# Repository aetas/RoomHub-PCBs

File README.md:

# RoomHub 3 PCBs

> :warning: RoomHub project is now deprecated in favor of [MqGateway](https://github.com/aetas/mqgateway) project.

<br />

Schematics and PCB design for RoomHub 3 MainBoard and IOBoard

Files can be read with [KiCad](https://kicad-pcb.org).

Read more about RoomHub on [documentation page](https://aetas.github.io/RoomHub/).

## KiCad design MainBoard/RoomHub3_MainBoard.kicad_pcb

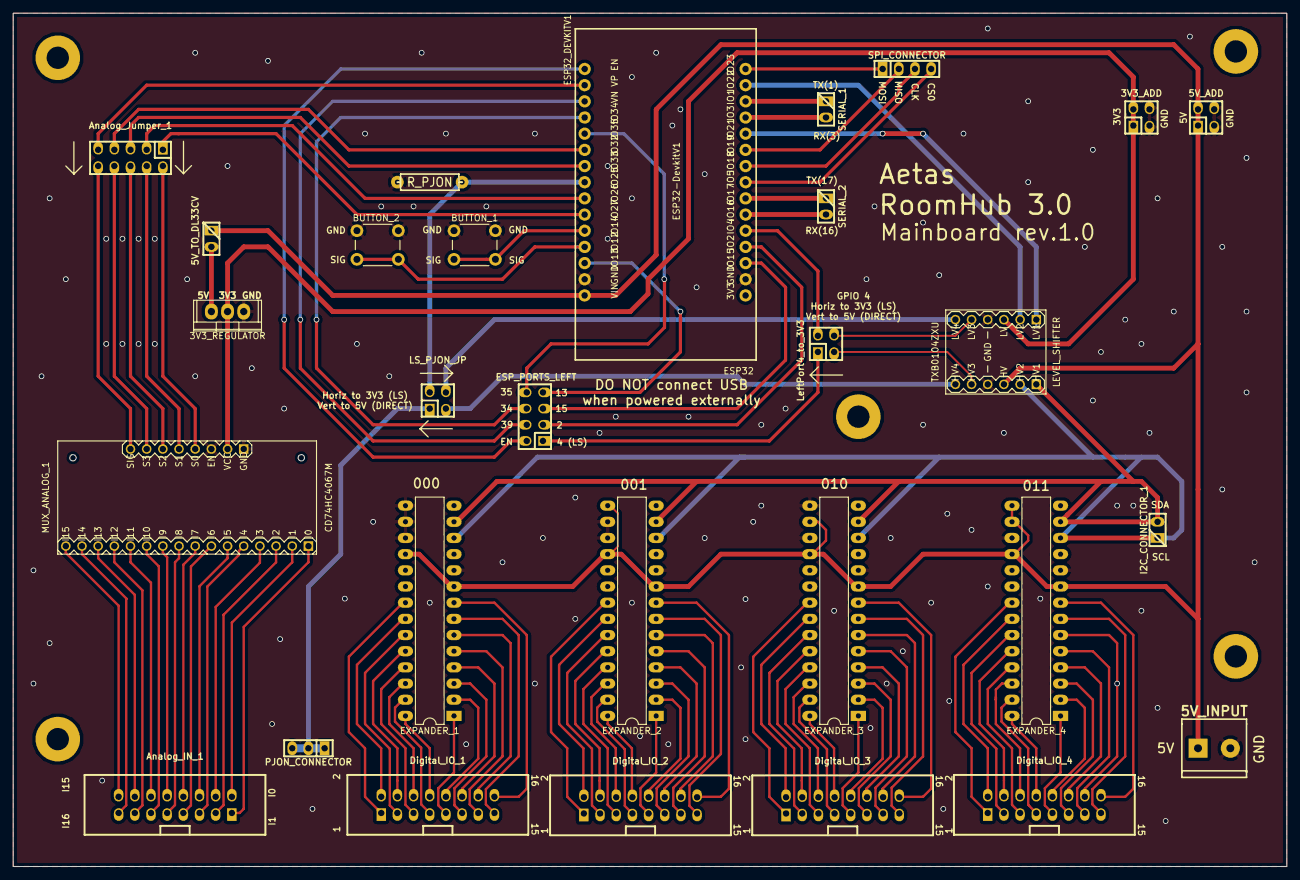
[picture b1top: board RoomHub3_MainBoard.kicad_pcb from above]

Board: 2 copper layers, 200.0 x 134.0 mm, 29 parts (0 on the bottom side), 123 nets.

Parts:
3V3_ADD, 5V_ADD: Conn_02x02_RAW; pin_strip_2x2
3V3_REGULATOR: LD33CV; TO-220
5V_INPUT: mors_2p
5V_TO_DL33CV: Jumper; pin_strip_2
Analog_IN_1: Conn_02x08_Counter_Clockwise; analog_conn_02x08
Analog_Jumper_1: Jumper_2x5; pin_strip_5x2
BUTTON_1, BUTTON_2: SW_Push; SW_PUSH_6mm
Digital_IO_1, Digital_IO_2, Digital_IO_3, Digital_IO_4: Conn_02x08_Counter_Clockwise; vasch_strip_8x2
ESP32: ESP32_DEVKITV1; ESP32-DEVKITV1
ESP_PORTS_LEFT: Conn_02x04_Counter_Clockwise; pin_strip_4x2
EXPANDER_1, EXPANDER_2, EXPANDER_3, EXPANDER_4: MCP23017_SP; DIP-28_W7.62mm_LongPads
I2C_CONNECTOR_1: Conn_01x02; pin_strip_2
LEVEL_SHIFTER: TXB0104ZXU; LEVEL-SHIFTER-4CH
LS_PJON_JP: Conn_02x02_RAW; pin_strip_2x2
LeftPort4_to_3V3: Conn_02x02_RAW; pin_strip_2x2
MUX_ANALOG_1: CD74HC4067M; SPARKFUN-AD-MUX-16X1-aetas
PJON_CONNECTOR: Conn_01x03; pin_strip_3
R_PJON: 2.2K; RC05
SERIAL_1, SERIAL_2: Conn_01x02; pin_strip_2
SPI_CONNECTOR: Conn_01x04; pin_strip_4

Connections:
+5V: 5V_ADD.1, 5V_ADD.2, 5V_INPUT.1, 5V_TO_DL33CV.1, ESP32.30, EXPANDER_1.9, EXPANDER_1.18, EXPANDER_2.9, EXPANDER_2.15, EXPANDER_2.18, EXPANDER_3.9, EXPANDER_3.16, EXPANDER_3.18, EXPANDER_4.9, EXPANDER_4.15, EXPANDER_4.16, EXPANDER_4.18, LEVEL_SHIFTER.B1
/3V3: 3V3_ADD.1, 3V3_ADD.2, 3V3_REGULATOR.2, LEVEL_SHIFTER.B2, MUX_ANALOG_1.24
/SCL1: ESP32.14, LEVEL_SHIFTER.A2
/SDA1: ESP32.11, LEVEL_SHIFTER.A1
GND: 3V3_ADD.3, 3V3_ADD.4, 3V3_REGULATOR.1, 5V_ADD.3, 5V_ADD.4, 5V_INPUT.2, BUTTON_1.1, BUTTON_2.1, ESP32.2, ESP32.29, EXPANDER_1.10, EXPANDER_1.15, EXPANDER_1.16, EXPANDER_1.17, EXPANDER_2.10, EXPANDER_2.16, EXPANDER_2.17, EXPANDER_3.10, EXPANDER_3.15, EXPANDER_3.17, EXPANDER_4.10, EXPANDER_4.17, LEVEL_SHIFTER.B3, LEVEL_SHIFTER.B4, MUX_ANALOG_1.12, MUX_ANALOG_1.15, R_PJON.1
unnamed: 3V3_REGULATOR.3, 5V_TO_DL33CV.2
unnamed: Analog_IN_1.1, MUX_ANALOG_1.9
unnamed: Analog_IN_1.2, MUX_ANALOG_1.8
unnamed: Analog_IN_1.3, MUX_ANALOG_1.7
unnamed: Analog_IN_1.4, MUX_ANALOG_1.6
unnamed: Analog_IN_1.5, MUX_ANALOG_1.5
unnamed: Analog_IN_1.6, MUX_ANALOG_1.4
unnamed: Analog_IN_1.7, MUX_ANALOG_1.3
unnamed: Analog_IN_1.8, MUX_ANALOG_1.2
unnamed: Analog_IN_1.9, MUX_ANALOG_1.23
unnamed: Analog_IN_1.10, MUX_ANALOG_1.22
unnamed: Analog_IN_1.11, MUX_ANALOG_1.21
unnamed: Analog_IN_1.12, MUX_ANALOG_1.20
unnamed: Analog_IN_1.13, MUX_ANALOG_1.19
unnamed: Analog_IN_1.14, MUX_ANALOG_1.18
unnamed: Analog_IN_1.15, MUX_ANALOG_1.17
unnamed: Analog_IN_1.16, MUX_ANALOG_1.16
unnamed: Analog_Jumper_1.1, ESP32.25
unnamed: Analog_Jumper_1.2, MUX_ANALOG_1.10
unnamed: Analog_Jumper_1.3, ESP32.24
unnamed: Analog_Jumper_1.4, MUX_ANALOG_1.11
unnamed: Analog_Jumper_1.5, ESP32.22
unnamed: Analog_Jumper_1.6, MUX_ANALOG_1.14
unnamed: Analog_Jumper_1.7, ESP32.21
unnamed: Analog_Jumper_1.8, MUX_ANALOG_1.13
unnamed: Analog_Jumper_1.9, ESP32.17
unnamed: Analog_Jumper_1.10, MUX_ANALOG_1.1
unnamed: Digital_IO_1.1, EXPANDER_1.21
unnamed: Digital_IO_1.2, EXPANDER_1.22
unnamed: Digital_IO_1.3, EXPANDER_1.23
unnamed: Digital_IO_1.4, EXPANDER_1.24
unnamed: Digital_IO_1.5, EXPANDER_1.25
unnamed: Digital_IO_1.6, EXPANDER_1.26
unnamed: Digital_IO_1.7, EXPANDER_1.27
unnamed: Digital_IO_1.8, EXPANDER_1.28
unnamed: Digital_IO_1.9, EXPANDER_1.1
unnamed: Digital_IO_1.10, EXPANDER_1.2
unnamed: Digital_IO_1.11, EXPANDER_1.3
unnamed: Digital_IO_1.12, EXPANDER_1.4
unnamed: Digital_IO_1.13, EXPANDER_1.5
unnamed: Digital_IO_1.14, EXPANDER_1.6
unnamed: Digital_IO_1.15, EXPANDER_1.7
unnamed: Digital_IO_1.16, EXPANDER_1.8
unnamed: Digital_IO_2.1, EXPANDER_2.21
unnamed: Digital_IO_2.2, EXPANDER_2.22
unnamed: Digital_IO_2.3, EXPANDER_2.23
unnamed: Digital_IO_2.4, EXPANDER_2.24
unnamed: Digital_IO_2.5, EXPANDER_2.25
unnamed: Digital_IO_2.6, EXPANDER_2.26
unnamed: Digital_IO_2.7, EXPANDER_2.27
unnamed: Digital_IO_2.8, EXPANDER_2.28
unnamed: Digital_IO_2.9, EXPANDER_2.1
unnamed: Digital_IO_2.10, EXPANDER_2.2
unnamed: Digital_IO_2.11, EXPANDER_2.3
unnamed: Digital_IO_2.12, EXPANDER_2.4
unnamed: Digital_IO_2.13, EXPANDER_2.5
unnamed: Digital_IO_2.14, EXPANDER_2.6
unnamed: Digital_IO_2.15, EXPANDER_2.7
unnamed: Digital_IO_2.16, EXPANDER_2.8
unnamed: Digital_IO_3.1, EXPANDER_3.21
unnamed: Digital_IO_3.2, EXPANDER_3.22
unnamed: Digital_IO_3.3, EXPANDER_3.23
unnamed: Digital_IO_3.4, EXPANDER_3.24
unnamed: Digital_IO_3.5, EXPANDER_3.25
unnamed: Digital_IO_3.6, EXPANDER_3.26
unnamed: Digital_IO_3.7, EXPANDER_3.27
unnamed: Digital_IO_3.8, EXPANDER_3.28
unnamed: Digital_IO_3.9, EXPANDER_3.1
unnamed: Digital_IO_3.10, EXPANDER_3.2
unnamed: Digital_IO_3.11, EXPANDER_3.3
unnamed: Digital_IO_3.12, EXPANDER_3.4
unnamed: Digital_IO_3.13, EXPANDER_3.5
unnamed: Digital_IO_3.14, EXPANDER_3.6
unnamed: Digital_IO_3.15, EXPANDER_3.7
unnamed: Digital_IO_3.16, EXPANDER_3.8
unnamed: Digital_IO_4.1, EXPANDER_4.21
unnamed: Digital_IO_4.2, EXPANDER_4.22
unnamed: Digital_IO_4.3, EXPANDER_4.23
unnamed: Digital_IO_4.4, EXPANDER_4.24
unnamed: Digital_IO_4.5, EXPANDER_4.25
unnamed: Digital_IO_4.6, EXPANDER_4.26
unnamed: Digital_IO_4.7, EXPANDER_4.27
unnamed: Digital_IO_4.8, EXPANDER_4.28
unnamed: Digital_IO_4.9, EXPANDER_4.1
unnamed: Digital_IO_4.10, EXPANDER_4.2
unnamed: Digital_IO_4.11, EXPANDER_4.3
unnamed: Digital_IO_4.12, EXPANDER_4.4
unnamed: Digital_IO_4.13, EXPANDER_4.5
unnamed: Digital_IO_4.14, EXPANDER_4.6
unnamed: Digital_IO_4.15, EXPANDER_4.7
unnamed: Digital_IO_4.16, EXPANDER_4.8
unnamed: ESP32.3, ESP_PORTS_LEFT.5
unnamed: ESP32.4, ESP_PORTS_LEFT.3
unnamed: ESP32.5, LeftPort4_to_3V3.2
unnamed: ESP32.6, SERIAL_2.2
unnamed: ESP32.7, SERIAL_2.1
unnamed: ESP32.8, SPI_CONNECTOR.4
unnamed: ESP32.9, SPI_CONNECTOR.3
unnamed: ESP32.10, SPI_CONNECTOR.2
unnamed: ESP32.12, SERIAL_1.2
unnamed: ESP32.13, SERIAL_1.1
unnamed: ESP32.15, SPI_CONNECTOR.1
unnamed: ESP32.16, ESP_PORTS_LEFT.2
unnamed: ESP32.18, ESP_PORTS_LEFT.4
unnamed: ESP32.19, ESP_PORTS_LEFT.6
unnamed: ESP32.20, ESP_PORTS_LEFT.8
unnamed: ESP32.23, LS_PJON_JP.2, R_PJON.2
unnamed: BUTTON_1.2, ESP32.26
unnamed: BUTTON_2.2, ESP32.27
unnamed: ESP32.28, ESP_PORTS_LEFT.7
unnamed: ESP_PORTS_LEFT.1, LeftPort4_to_3V3.1
unnamed: EXPANDER_1.12, EXPANDER_2.12, EXPANDER_3.12, EXPANDER_4.12, I2C_CONNECTOR_1.1, LEVEL_SHIFTER.C2
unnamed: EXPANDER_1.13, EXPANDER_2.13, EXPANDER_3.13, EXPANDER_4.13, I2C_CONNECTOR_1.2, LEVEL_SHIFTER.C1
unnamed: LEVEL_SHIFTER.A3, LeftPort4_to_3V3.4
unnamed: LEVEL_SHIFTER.A4, LS_PJON_JP.4
unnamed: LEVEL_SHIFTER.C3, LeftPort4_to_3V3.3
unnamed: LEVEL_SHIFTER.C4, LS_PJON_JP.3
unnamed: LS_PJON_JP.1, PJON_CONNECTOR.1, PJON_CONNECTOR.2, PJON_CONNECTOR.3

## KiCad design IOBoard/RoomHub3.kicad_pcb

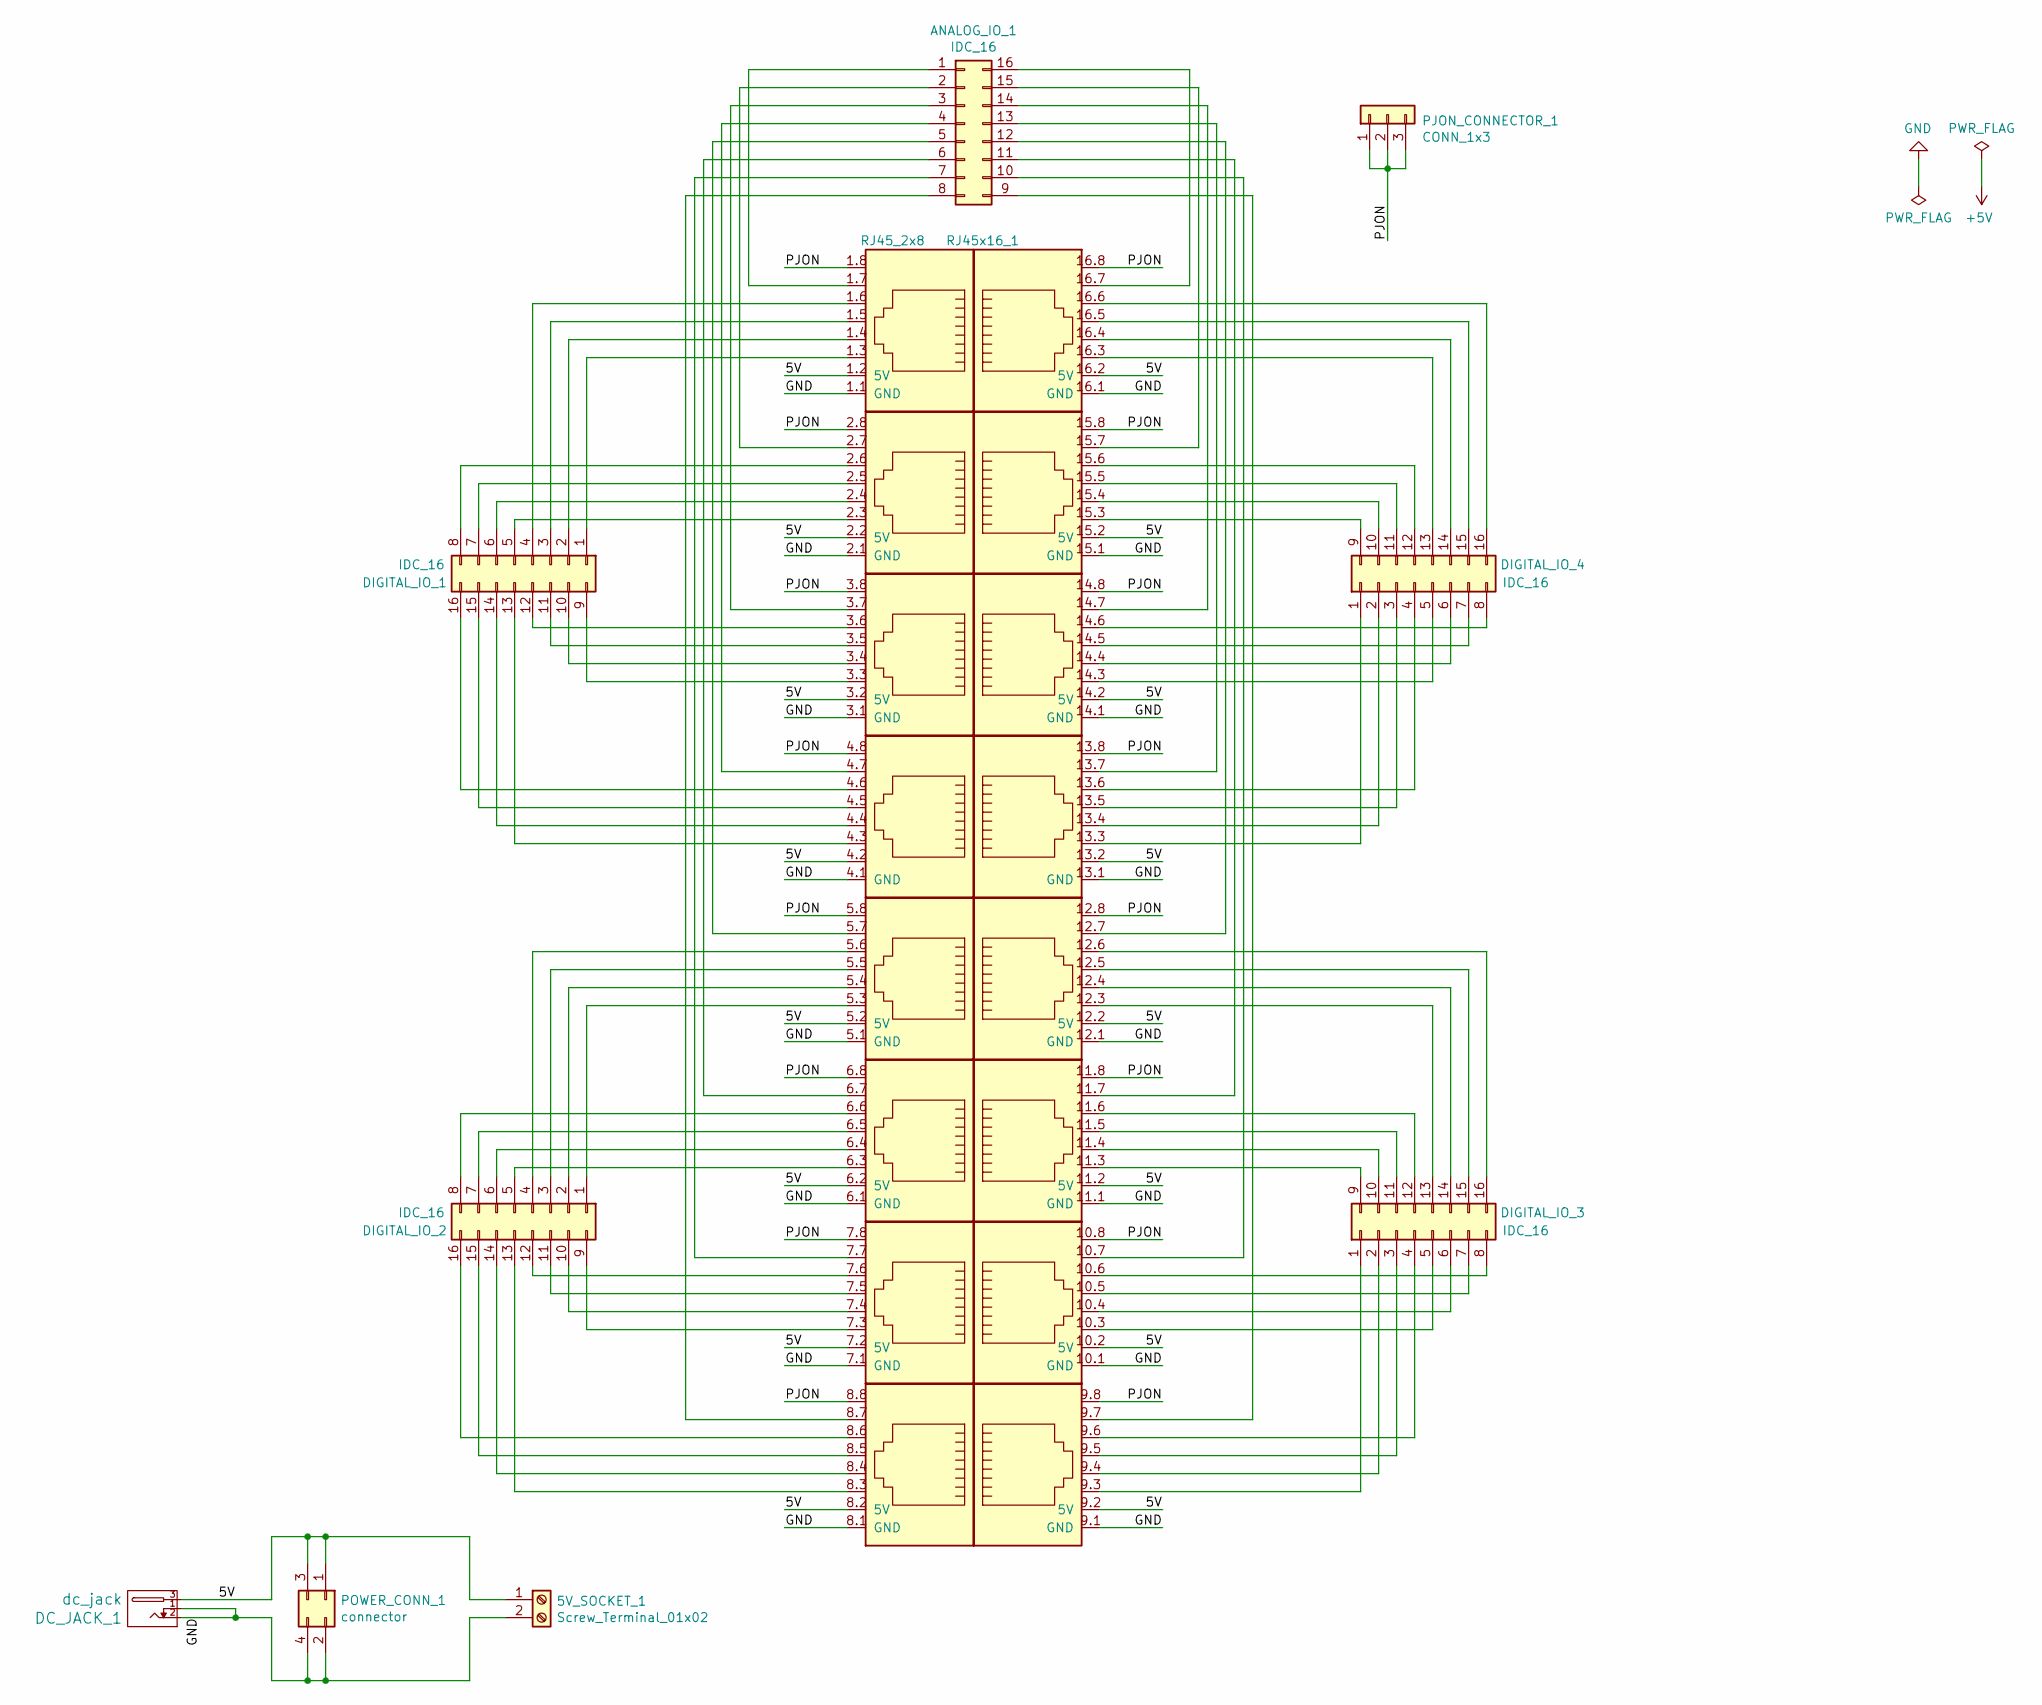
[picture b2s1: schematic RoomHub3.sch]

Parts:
5V_SOCKET_1: Screw_Terminal_01x02; mors_2p
ANALOG_IO_1: IDC_16; analog_conn_02x08
DC_JACK_1: dc_jack; dc_socket
DIGITAL_IO_1, DIGITAL_IO_2, DIGITAL_IO_3, DIGITAL_IO_4: IDC_16; vasch_strip_8x2
PJON_CONNECTOR_1: CONN_1x3; pin_strip_3
POWER_CONN_1: connector; pin_strip_2x2
RJ45x16_1: RJ45_2x8; 8p8c_2x8_roomhub

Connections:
/5V: 5V_SOCKET_1.1, DC_JACK_1.3, POWER_CONN_1.1, POWER_CONN_1.3, RJ45x16_1.1.2 (5V), RJ45x16_1.2.2 (5V), RJ45x16_1.3.2 (5V), RJ45x16_1.4.2, RJ45x16_1.5.2 (5V), RJ45x16_1.6.2 (5V), RJ45x16_1.7.2 (5V), RJ45x16_1.8.2 (5V), RJ45x16_1.9.2 (5V), RJ45x16_1.10.2 (5V), RJ45x16_1.11.2 (5V), RJ45x16_1.12.2 (5V), RJ45x16_1.13.2, RJ45x16_1.14.2 (5V), RJ45x16_1.15.2 (5V), RJ45x16_1.16.2 (5V)
/PJON: PJON_CONNECTOR_1.1, PJON_CONNECTOR_1.2, PJON_CONNECTOR_1.3, RJ45x16_1.1.8, RJ45x16_1.2.8, RJ45x16_1.3.8, RJ45x16_1.4.8, RJ45x16_1.5.8, RJ45x16_1.6.8, RJ45x16_1.7.8, RJ45x16_1.8.8, RJ45x16_1.9.8, RJ45x16_1.10.8, RJ45x16_1.11.8, RJ45x16_1.12.8, RJ45x16_1.13.8, RJ45x16_1.14.8, RJ45x16_1.15.8, RJ45x16_1.16.8
GND: 5V_SOCKET_1.2, DC_JACK_1.1, DC_JACK_1.2, POWER_CONN_1.2, POWER_CONN_1.4, RJ45x16_1.1.1 (GND), RJ45x16_1.2.1 (GND), RJ45x16_1.3.1 (GND), RJ45x16_1.4.1 (GND), RJ45x16_1.5.1 (GND), RJ45x16_1.6.1 (GND), RJ45x16_1.7.1 (GND), RJ45x16_1.8.1 (GND), RJ45x16_1.9.1 (GND), RJ45x16_1.10.1 (GND), RJ45x16_1.11.1 (GND), RJ45x16_1.12.1 (GND), RJ45x16_1.13.1 (GND), RJ45x16_1.14.1 (GND), RJ45x16_1.15.1 (GND), RJ45x16_1.16.1 (GND)
unnamed: ANALOG_IO_1.1, RJ45x16_1.1.7
unnamed: ANALOG_IO_1.2, RJ45x16_1.2.7
unnamed: ANALOG_IO_1.3, RJ45x16_1.3.7
unnamed: ANALOG_IO_1.4, RJ45x16_1.4.7
unnamed: ANALOG_IO_1.5, RJ45x16_1.5.7
unnamed: ANALOG_IO_1.6, RJ45x16_1.6.7
unnamed: ANALOG_IO_1.7, RJ45x16_1.7.7
unnamed: ANALOG_IO_1.8, RJ45x16_1.8.7
unnamed: ANALOG_IO_1.9, RJ45x16_1.9.7
unnamed: ANALOG_IO_1.10, RJ45x16_1.10.7
unnamed: ANALOG_IO_1.11, RJ45x16_1.11.7
unnamed: ANALOG_IO_1.12, RJ45x16_1.12.7
unnamed: ANALOG_IO_1.13, RJ45x16_1.13.7
unnamed: ANALOG_IO_1.14, RJ45x16_1.14.7
unnamed: ANALOG_IO_1.15, RJ45x16_1.15.7
unnamed: ANALOG_IO_1.16, RJ45x16_1.16.7
unnamed: DIGITAL_IO_1.1, RJ45x16_1.1.3
unnamed: DIGITAL_IO_1.2, RJ45x16_1.1.4
unnamed: DIGITAL_IO_1.3, RJ45x16_1.1.5
unnamed: DIGITAL_IO_1.4, RJ45x16_1.1.6
unnamed: DIGITAL_IO_1.5, RJ45x16_1.2.3
unnamed: DIGITAL_IO_1.6, RJ45x16_1.2.4
unnamed: DIGITAL_IO_1.7, RJ45x16_1.2.5
unnamed: DIGITAL_IO_1.8, RJ45x16_1.2.6
unnamed: DIGITAL_IO_1.9, RJ45x16_1.3.3
unnamed: DIGITAL_IO_1.10, RJ45x16_1.3.4
unnamed: DIGITAL_IO_1.11, RJ45x16_1.3.5
unnamed: DIGITAL_IO_1.12, RJ45x16_1.3.6
unnamed: DIGITAL_IO_1.13, RJ45x16_1.4.3
unnamed: DIGITAL_IO_1.14, RJ45x16_1.4.4
unnamed: DIGITAL_IO_1.15, RJ45x16_1.4.5
unnamed: DIGITAL_IO_1.16, RJ45x16_1.4.6
unnamed: DIGITAL_IO_2.1, RJ45x16_1.5.3
unnamed: DIGITAL_IO_2.2, RJ45x16_1.5.4
unnamed: DIGITAL_IO_2.3, RJ45x16_1.5.5
unnamed: DIGITAL_IO_2.4, RJ45x16_1.5.6
unnamed: DIGITAL_IO_2.5, RJ45x16_1.6.3
unnamed: DIGITAL_IO_2.6, RJ45x16_1.6.4
unnamed: DIGITAL_IO_2.7, RJ45x16_1.6.5
unnamed: DIGITAL_IO_2.8, RJ45x16_1.6.6
unnamed: DIGITAL_IO_2.9, RJ45x16_1.7.3
unnamed: DIGITAL_IO_2.10, RJ45x16_1.7.4
unnamed: DIGITAL_IO_2.11, RJ45x16_1.7.5
unnamed: DIGITAL_IO_2.12, RJ45x16_1.7.6
unnamed: DIGITAL_IO_2.13, RJ45x16_1.8.3
unnamed: DIGITAL_IO_2.14, RJ45x16_1.8.4
unnamed: DIGITAL_IO_2.15, RJ45x16_1.8.5
unnamed: DIGITAL_IO_2.16, RJ45x16_1.8.6
unnamed: DIGITAL_IO_3.1, RJ45x16_1.9.3
unnamed: DIGITAL_IO_3.2, RJ45x16_1.9.4
unnamed: DIGITAL_IO_3.3, RJ45x16_1.9.5
unnamed: DIGITAL_IO_3.4, RJ45x16_1.9.6
unnamed: DIGITAL_IO_3.5, RJ45x16_1.10.3
unnamed: DIGITAL_IO_3.6, RJ45x16_1.10.4
unnamed: DIGITAL_IO_3.7, RJ45x16_1.10.5
unnamed: DIGITAL_IO_3.8, RJ45x16_1.10.6
unnamed: DIGITAL_IO_3.9, RJ45x16_1.11.3
unnamed: DIGITAL_IO_3.10, RJ45x16_1.11.4
unnamed: DIGITAL_IO_3.11, RJ45x16_1.11.5
unnamed: DIGITAL_IO_3.12, RJ45x16_1.11.6
unnamed: DIGITAL_IO_3.13, RJ45x16_1.12.3
unnamed: DIGITAL_IO_3.14, RJ45x16_1.12.4
unnamed: DIGITAL_IO_3.15, RJ45x16_1.12.5
unnamed: DIGITAL_IO_3.16, RJ45x16_1.12.6
unnamed: DIGITAL_IO_4.1, RJ45x16_1.13.3
unnamed: DIGITAL_IO_4.2, RJ45x16_1.13.4
unnamed: DIGITAL_IO_4.3, RJ45x16_1.13.5
unnamed: DIGITAL_IO_4.4, RJ45x16_1.13.6
unnamed: DIGITAL_IO_4.5, RJ45x16_1.14.3
unnamed: DIGITAL_IO_4.6, RJ45x16_1.14.4
unnamed: DIGITAL_IO_4.7, RJ45x16_1.14.5
unnamed: DIGITAL_IO_4.8, RJ45x16_1.14.6
unnamed: DIGITAL_IO_4.9, RJ45x16_1.15.3
unnamed: DIGITAL_IO_4.10, RJ45x16_1.15.4
unnamed: DIGITAL_IO_4.11, RJ45x16_1.15.5
unnamed: DIGITAL_IO_4.12, RJ45x16_1.15.6
unnamed: DIGITAL_IO_4.13, RJ45x16_1.16.3
unnamed: DIGITAL_IO_4.14, RJ45x16_1.16.4
unnamed: DIGITAL_IO_4.15, RJ45x16_1.16.5
unnamed: DIGITAL_IO_4.16, RJ45x16_1.16.6

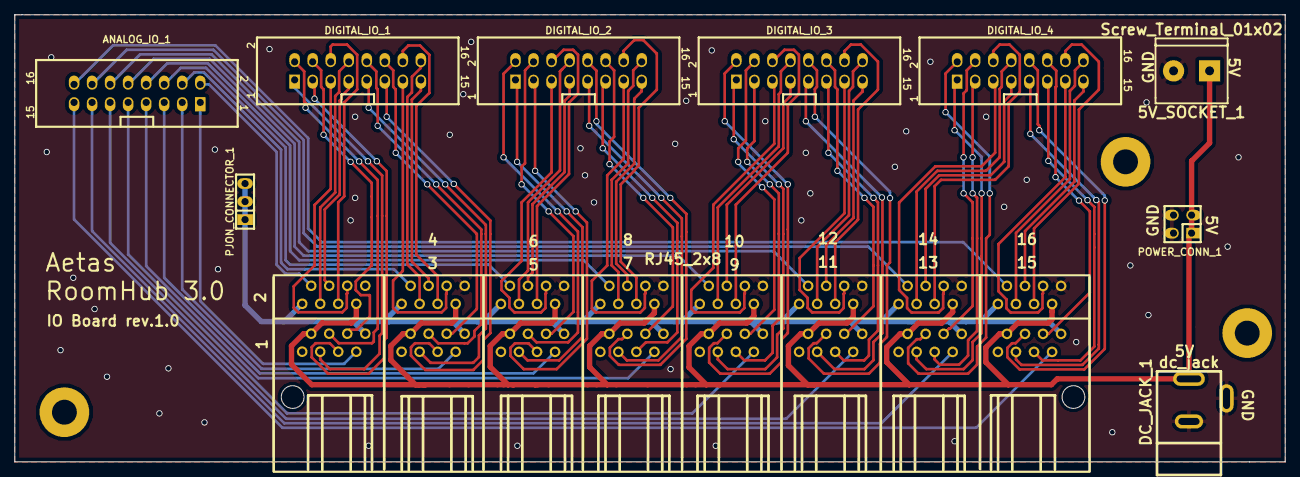
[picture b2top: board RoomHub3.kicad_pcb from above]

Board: 2 copper layers, 179.0 x 63.0 mm, 9 parts (0 on the bottom side), 3 nets.

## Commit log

2020-02-17 Adding MainBoard and IOBoard schematics and PCB designs
2020-02-17 README created
2021-01-16 Deprecation information
